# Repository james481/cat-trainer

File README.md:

# Cat Trainer

## Electronic Feline Warfare for Fun and Profit

![Cat Trainer][main]

A microcontroller based system for training cats using accelerometer based sensors to detect clawing of carpet or furniture and automatically discouraging the behavior using sprayed water.

See more details about this project and how it was built [here](https://james481.github.io/cat-trainer/).

__This project has been featured on [Hackaday](http://hackaday.com/2017/01/20/sentry-robot-turns-bad-cat-to-good/). Welcome HaD readers and thanks for checking it out!__

* [Base Software](./base/teensy_base)
* [Base PCB - OSHPark](https://oshpark.com/shared_projects/nA5DhVjQ)
* [Base KiCad Schematic / PCB](./base/teensy_base_pcb)
* [Sensor Software](./sensor/arduino_mma8452)
* [Sensor PCB - OSHPark](https://oshpark.com/shared_projects/1HsJuNbs)
* [Sensor KiCad Schematic / PCB](./sensor/feather32u4_mma8452_pcb)

All code and other materials contained in this repository are copyright (c) 2016 - 2017 James Watts or their respective copyright holders as noted, and is provided under BSD license. For details see [LICENSE.txt](LICENSE.txt).

This device is patent pending. Please [contact me](http://www.jamescwatts.com) for licensing or more information.

[main]: ./docs/img/main_realistic.png

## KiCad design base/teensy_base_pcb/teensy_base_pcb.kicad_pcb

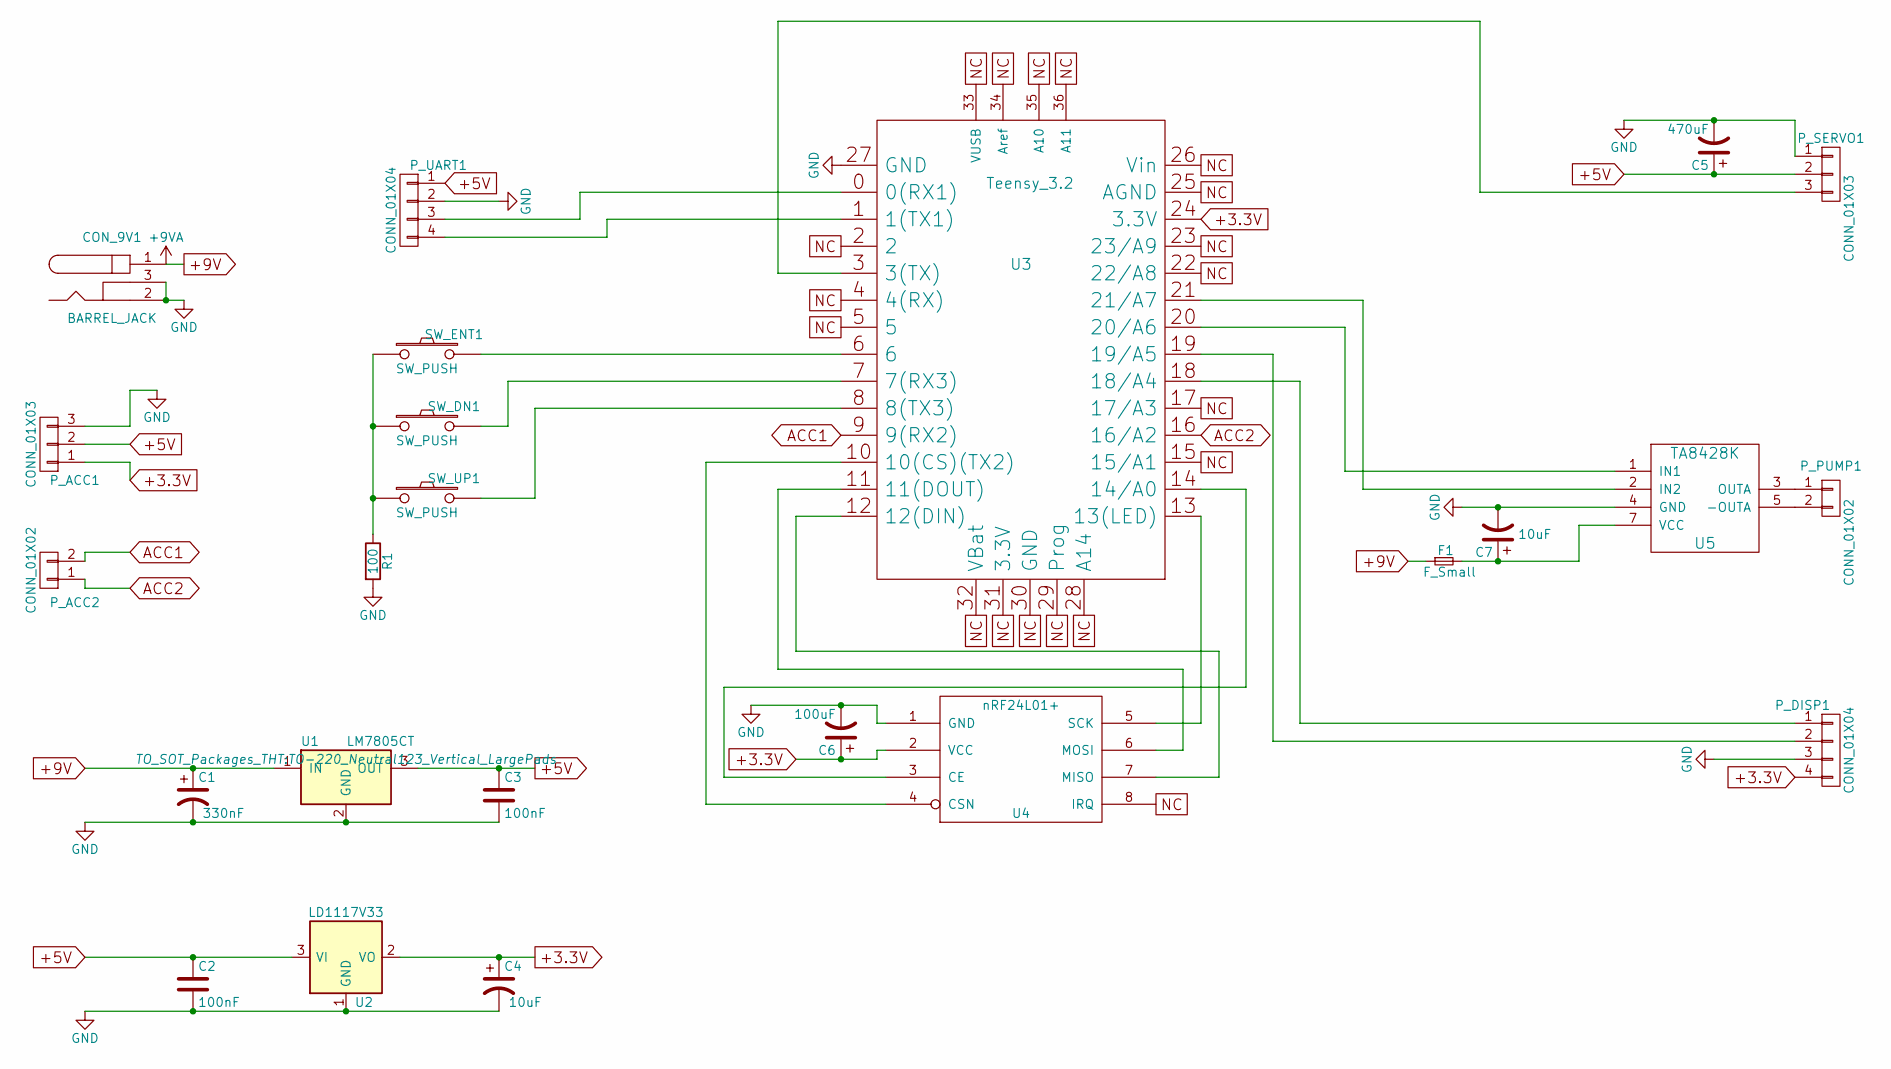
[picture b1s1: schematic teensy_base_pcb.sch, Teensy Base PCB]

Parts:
C1: 330nF; C_Rect_L7_W2.5_P5
C2, C3: 100nF; C_Rect_L7_W2.5_P5
C4, C7: 10uF; C_Rect_L7_W2.5_P5
C5: 470uF; C_Radial_D8_L13_P3.8
C6: 100uF; C_Radial_D5_L11_P2.5
CON_9V1: BARREL_JACK
F1: F_Small; Fuse_TE5_Littlefuse-395Series
P_ACC1: CONN_01X03; Pin_Header_Straight_1x03
P_ACC2: CONN_01X02; Pin_Header_Straight_1x02
P_DISP1: CONN_01X04; Pin_Header_Angled_1x04
P_PUMP1: CONN_01X02; TerminalBlock_Pheonix_PT-3.5mm_2pol
P_SERVO1: CONN_01X03; Pin_Header_Angled_1x03
P_UART1: CONN_01X04; Socket_Strip_Angled_1x04
R1: 100; Resistor_Horizontal_RM10mm
SW_DN1: SW_PUSH; Pin_Header_Angled_1x02
SW_ENT1: SW_PUSH; Pin_Header_Angled_1x02
SW_UP1: SW_PUSH; Pin_Header_Angled_1x02
U1: LM7805CT; TO-220_Neutral123_Vertical_LargePads
U2: LD1117V33; TO-220_Neutral123_Vertical_LargePads
U3: Teensy_3.2; Teensy-3.1
U4: nRF24L01+; Socket_Strip_Straight_2x04
U5: TA8428K; Socket_Strip_Straight_1x07

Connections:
+3.3V: C4.1, C6.1, P_ACC1.1, P_DISP1.4, U2.2 (VO), U3.24 (3.3V), U4.2 (VCC)
+5V: C2.1, C3.1, C5.1, P_ACC1.2, P_SERVO1.2, P_UART1.1, U1.3 (OUT), U2.3 (VI)
+9V: C1.1, CON_9V1.1, F1.1, U1.1 (IN)
ACC1: P_ACC2.2, U3.9 (9(RX2))
ACC2: P_ACC2.1, U3.16 (16/A2)
GND: C1.2, C2.2, C3.2, C4.2, C5.2, C6.2, C7.2, CON_9V1.2, CON_9V1.3, P_ACC1.3, P_DISP1.3, P_SERVO1.1, P_UART1.2, R1.2, U1.2 (GND), U2.1 (GND), U3.27 (GND), U4.1 (GND), U5.4 (GND)
NC: U3.2, U3.4 (4(RX)), U3.5, U3.15 (15/A1), U3.17 (17/A3), U3.22 (22/A8), U3.23 (23/A9), U3.25 (AGND), U3.26 (Vin), U3.28 (A14), U3.29 (Prog), U3.30 (GND), U3.31 (3.3V), U3.32 (VBat), U3.33 (VUSB), U3.34 (Aref), U3.35 (A10), U3.36 (A11), U4.8 (IRQ)
unnamed: C7.1, F1.2, U5.7 (VCC)
unnamed: P_DISP1.1, U3.18 (18/A4)
unnamed: P_DISP1.2, U3.19 (19/A5)
unnamed: P_PUMP1.1, U5.3 (OUTA)
unnamed: P_PUMP1.2, U5.5 (-OUTA)
unnamed: P_SERVO1.3, U3.3 (3(TX))
unnamed: P_UART1.3, U3.0 (0(RX1))
unnamed: P_UART1.4, U3.1 (1(TX1))
unnamed: R1.1, SW_DN1.1, SW_ENT1.1, SW_UP1.1
unnamed: SW_DN1.2, U3.7 (7(RX3))
unnamed: SW_ENT1.2, U3.6
unnamed: SW_UP1.2, U3.8 (8(TX3))
unnamed: U3.10 (10(CS)(TX2)), U4.4 (CSN)
unnamed: U3.11 (11(DOUT)), U4.6 (MOSI)
unnamed: U3.12 (12(DIN)), U4.7 (MISO)
unnamed: U3.13 (13(LED)), U4.5 (SCK)
unnamed: U3.14 (14/A0), U4.3 (CE)
unnamed: U3.20 (20/A6), U5.1 (IN1)
unnamed: U3.21 (21/A7), U5.2 (IN2)

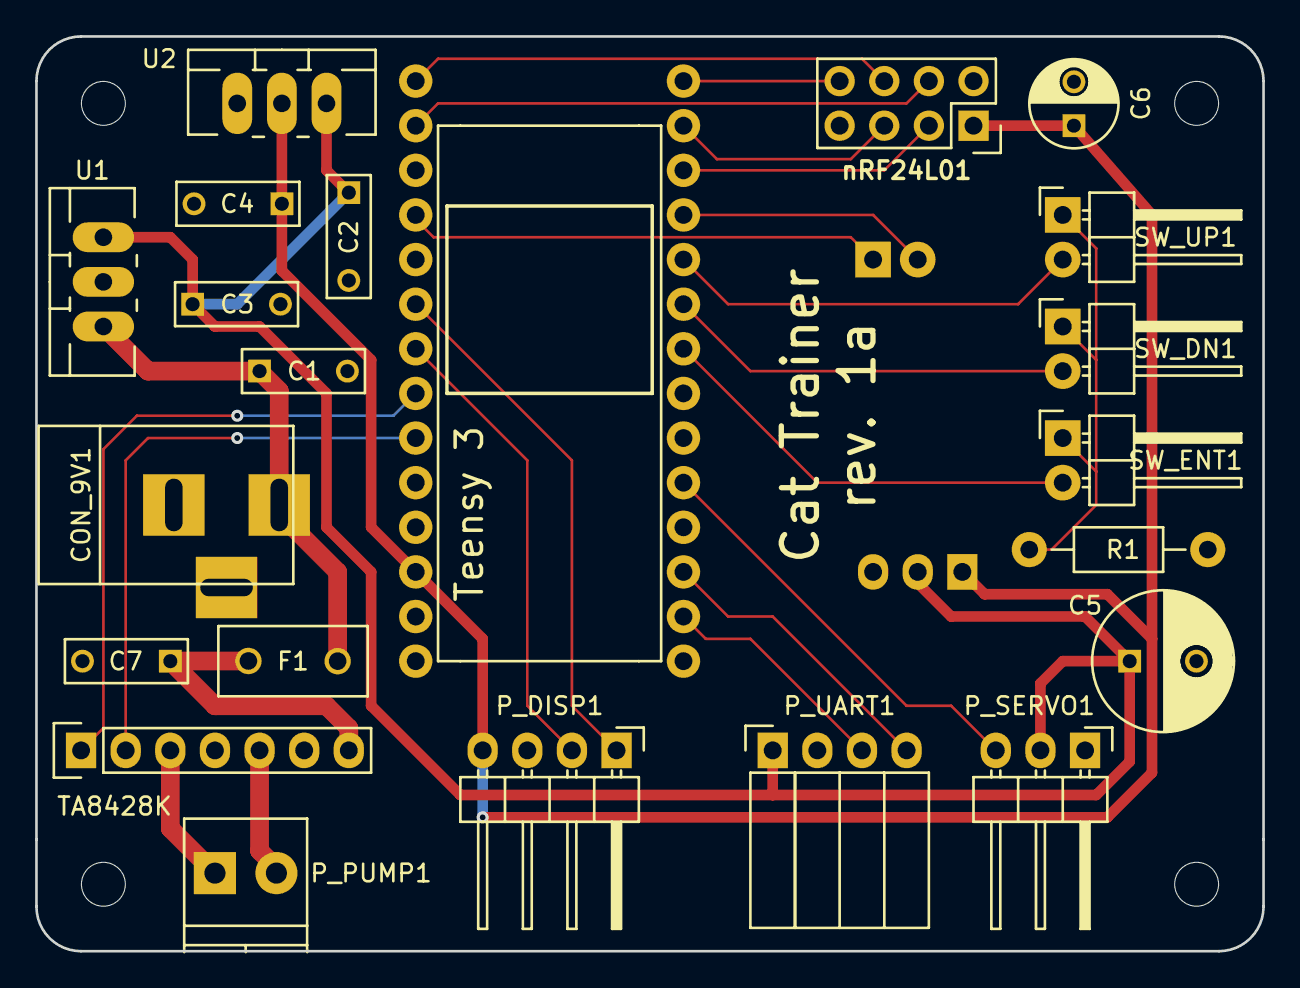
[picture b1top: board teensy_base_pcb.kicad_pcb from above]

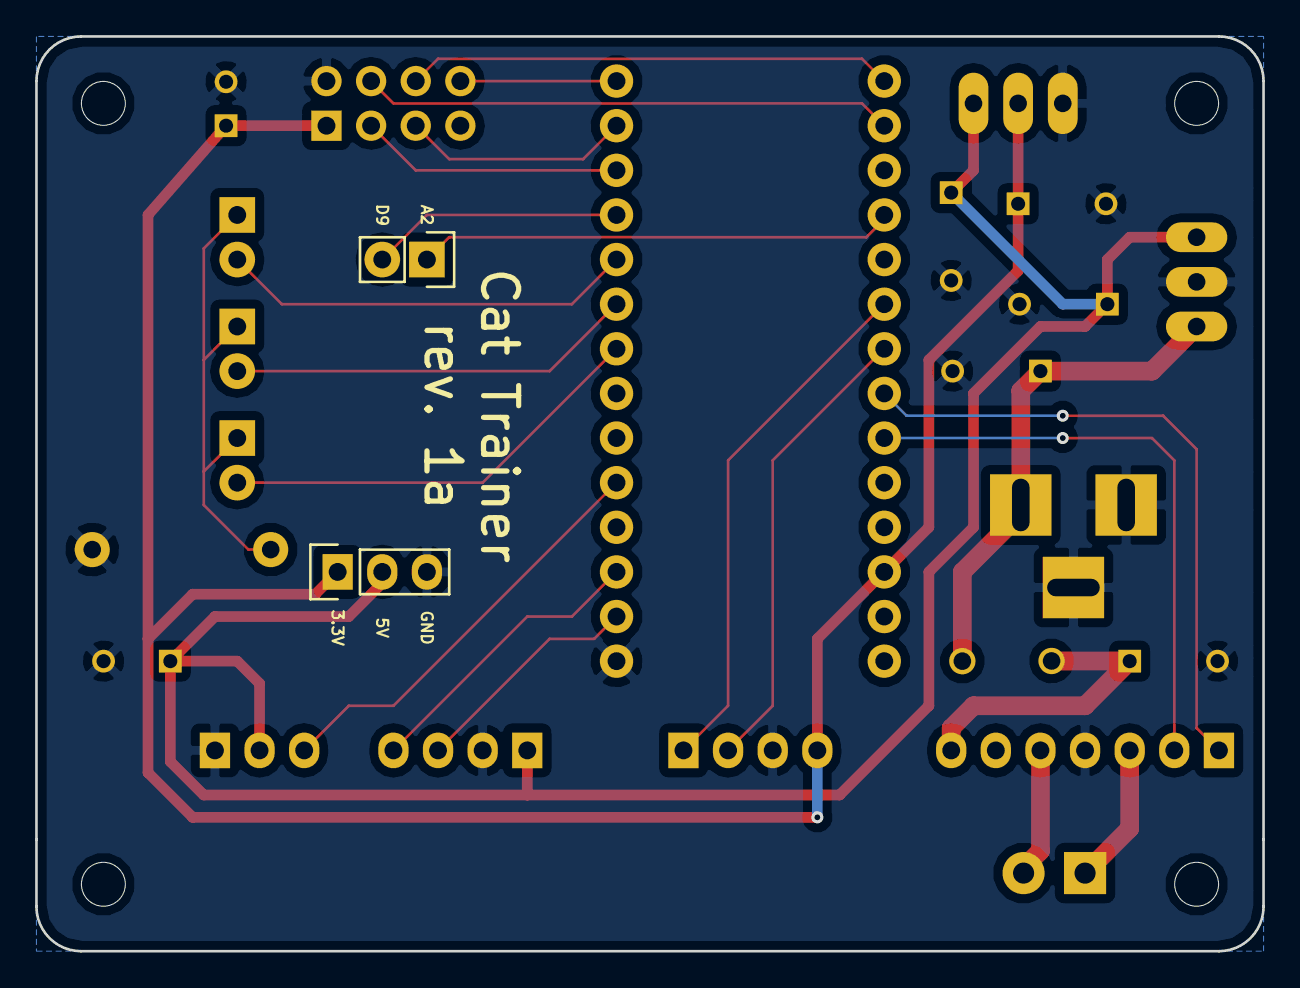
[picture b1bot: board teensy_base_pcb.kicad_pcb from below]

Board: 2 copper layers, 69.9 x 52.1 mm, 24 parts (2 on the bottom side), 26 nets.

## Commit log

2016-02-02 Initial commit / README
    Add base of arduino_mma8452 sensor code
2016-02-03 Add interrupt handling and I2C helper functions to arduino_mma8452.
2016-02-07 MMA8452 Sensor setup / timers setup / interrupts setup / status LED
2016-02-07 Move LED on timer to Timer2 (Timer1 doesn't wake up the chip).
2016-02-07 Add Feather 32u4 Battery voltage monitor code.
    Add LED color convenience method.
2016-02-07 Add radio send packet on sensor activate (incomplete).
    Add radio / printf debugging.
    Turn off LED on start.
    Clean up debug logging.
    Delay status LED flash on sensor LED flash.
2016-02-09 Add sensor radio payload struct / send.
    Flash yellow on failed / timeout send.
    Power down radio after sending.
2016-02-14 Add data packet structures
    Read UID struct from EEPROM (static for debug)
    Organize includes / clean up logging
2016-02-28 Add sensor sync and status packets sending for MMA8452
    Add RPi / python sensor test script
    Add Feather 32u4 gpio pin defines for MMA8452
    Add dynamic writing pipe selection from sync packet for MMA8452
2016-02-28 Add single data packet struct for all packets
    Clean up packet type numbering
    Clean up RPi sensor test script and update for new packet format
    Add length checking to status and trigger packet recv
2016-08-14 Feather 32u4 timer / interrupt changes.
2016-08-31 Sensor EEPROM id write script
2016-09-17 Teensy base station, initial commit.
2016-09-18 Base station menu classes / handling (incomplete).
2016-09-18 Store display and root item as pointers in MenuDisplay.
    Clean up debugging messages.
2016-09-25 Add base servo / spray / radio state handling (incomplete).
2016-09-25 Add handleSyncRequest to syncronize new / existing sensors.
    Add acknowledgeSensor to send OK response to sensor packets.
    Add desyncronizeSensor to remove / reset sensor id and force resync.
    Update handleRadioPacket for new sub methods.
    Add copyFrom convenience method to SensorUid class.
2016-09-25 Clean up base / sensor pipe addresses for send / recv.
    Add handleSensorData and handleSensorStatus methods to base.
    Change float vbat to uint in DataPacket.
    Add common ct_sensor include to arduino_mma8452 sensor.
2016-09-26 Add Active / Label callback closures to MenuItem class.
    Add active and label callbacks for sensor menu items.
    Clean up extra debug messages.
    Clean up returns on MenuItem fluent interface.
2016-09-26 Add sensor status display menu items.
    Add child and value callbacks to menu items.
2016-09-26 Add editing / editable state to MenuDisplay and MenuItem.
    Add edit callbacks for sensor dir / active and master active.
2016-09-28 Add status display screen w/ sensors, master active and WL.
    Clean up menu interactions and bugs.
    Add activated count to sensor storage.
    Clean up / align power on splash screen.
2016-10-01 Update debug logging messages to be consistent.
    Update pinout defines for updated Feather32u4 hardware.
    Add desync packet support to MMA8452 sensor.
2016-10-02 Draw battery voltage level on sensor icon.
    Add display dim timeout.
    Set sensor edit menu item parent items on sensor child cb.
    Only increment sensor activated count if sensor is active.
2016-10-18 Add Base PCB design files.
2016-10-19 PCB updates / clean up.
2016-10-22 More PCB clean up / labels.
2016-10-22 Add accessory / future expansion ports to PCB.
2016-10-22 Reverse PCB Acc 3.3 / 5V pins and clean up traces.
2016-10-28 Update schematic for motor driver / component.
    Update capacitor footprints.
2016-10-29 Update PCB layout for TA8428K motor driver.
2016-10-29 Clean up traces and fill areas.
2016-10-29 Add resettable fuse / clean up traces / widths.
2016-10-29 Swap servo output pins and clean up traces.
2016-10-30 Increase current trace size and clean up labels.
2016-10-30 Move button resistor and more track clean up.
2016-10-30 More trace cleanup.
2016-10-31 Add document title / rev and set button R value.
2016-10-31 Rebuild plane fill / final DRC check.
2016-10-31 Update barrel jack for round drill restriction at OSHPark.
2016-11-04 Update base code for PCB pin updates / TA8428 driver / internal pullup.
2016-11-06 Adding initial FreeCAD base model.
2016-11-06 More CAD modeling of base.
2016-11-07 Add servo / spray nozzle parts to base CAD.
    Add FreeCAD backup files to gitignore.
2016-11-08 Add tripod to base CAD.
2016-11-16 Add hoses and wires.
2016-11-27 Add arduino_mma8452 sensor CAD (incomplete).
    Clean up sketch / layer visibility on base CAD.
2016-11-27 More updates on arduino_mma8452 CAD.
2016-11-27 Complete MMA8452 sensor CAD.
2016-11-27 Cut hole for LED in arduino_mma8452 CAD.
    Clean up material rendering / set transparencies on CAD models.
2016-11-27 Improve MMA8452 CAD USB connector.
2016-11-27 Remove unneeded geometry from MMA8452 CAD.
2016-12-04 Feather 32u4 / MMA8452 sensor PCB
2016-12-06 Clean up wires on arduino_mma8452 CAD.
2016-12-21 Update base for add menu items and fix sensor code for PCB (inc).
2017-01-16 Clean up export visibility on base FreeCAD model.
2017-01-16 Add testing docs folder for GH pages.
2017-01-16 Set theme jekyll-theme-midnight
2017-01-17 Main GH pages page markdown (incomplete).
2017-01-18 Update main build page / add images.
2017-01-18 More main page / readme / config updates.
2017-01-18 Add LICENSE.txt BSD license file and copyright file headers.
    More README and main doc updates.
2017-01-18 Fix repository links in GH Pages index.
2017-01-19 Add Imgur high res link.
2017-01-19 Update GH build page images to serve from Imgur.
2017-01-20 Add Hackaday feature welcome / update text.
2017-01-20 README minor text / HaD welcome update.
2017-01-20 Add patent licensing text / update to README and GH pages.
